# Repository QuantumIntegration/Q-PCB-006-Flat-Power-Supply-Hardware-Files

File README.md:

# Quantum DIY Kit Hardware Files - Flat Power Supply
## Introduction

This repository contains all the hardware files necessary to build the PCBs and assemble the DIY kits. The PCBs can be ordered from for example [JLCPCB](https://jlcpcb.com/) or [PCBWay](https://www.pcbway.com/). The components can be sourced mostly from [Amazon](https://amazon.com/) or [Digikey](https://digikey.com/), according to the links in the BOM file.

## Download the correct revision

If you are nor familiar with the git version control system, please follow these simple steps to download your version of the DIY kit

<em>1. Click the branch button</em>

<em>2. Select the branch matching your revision</em>

<em>3. Click the Code button</em>

<em>4. Download the ZIP and extract it on your machine</em>

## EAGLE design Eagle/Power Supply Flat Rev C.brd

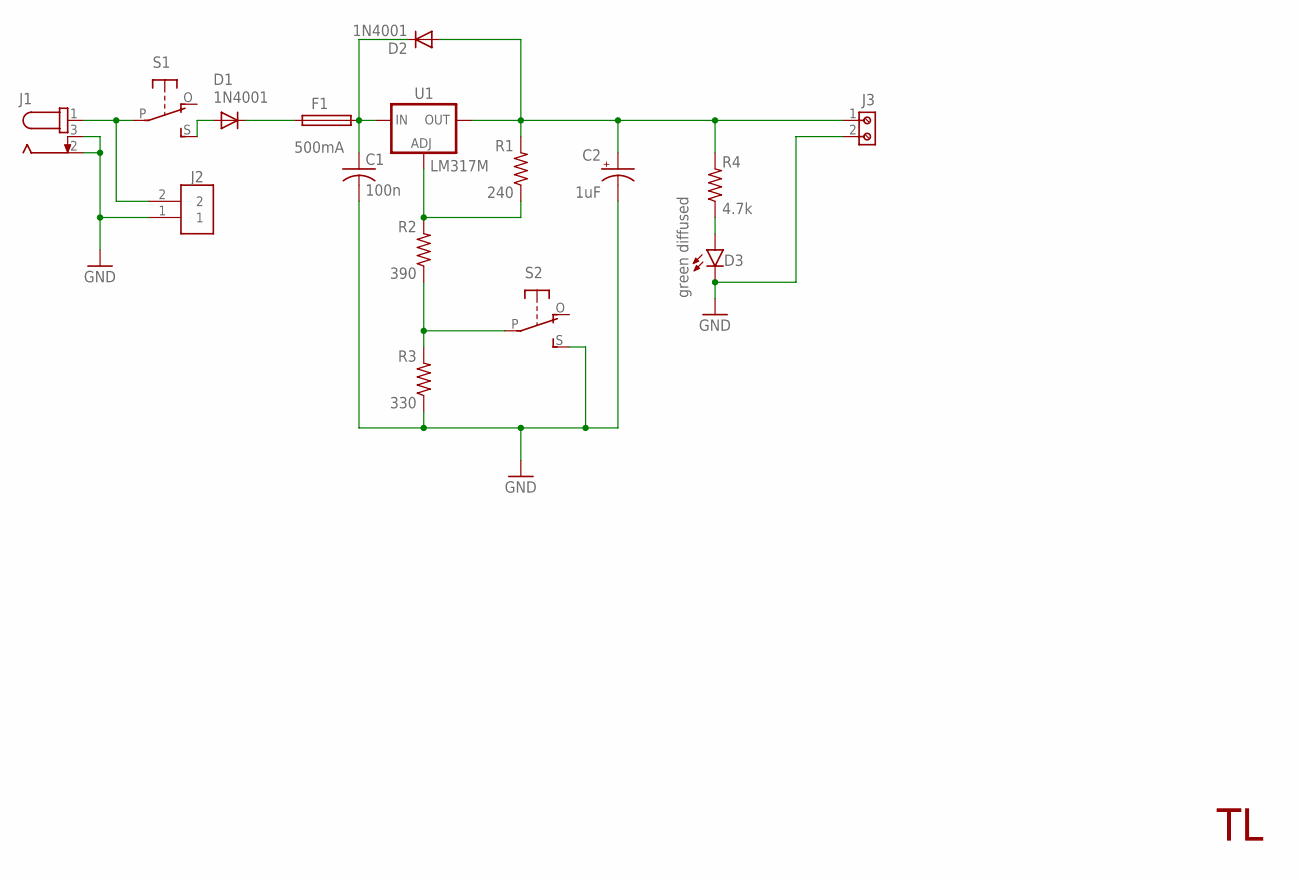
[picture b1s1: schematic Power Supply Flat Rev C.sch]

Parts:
C1: 100n; C050-024X044
C2: 1uF; E2-4
D1, D2: 1N4001; DO41-10
D3: green diffused; LED5MM
F1: 500mA; PTC-FUSE
J1: 694106301002
J2: 61300211121
J3: 691214110002
R1: 240; 0207/10
R2: 390; 0207/10
R3: 330; 0207/10
R4: 4.7k; 0207/10
S1, S2: SLIDE-SWITCHSIDE; EG1270-90
U1: LM317BENT; T03B; PARTNUMBER LM317M

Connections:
GND: C1.2, C2.-, D3.K (C), J1.2, J1.3, J2.1, J3.2, R3.1, S2.S
unnamed: D1.A, S1.S
unnamed: J1.1, J2.2, S1.P
unnamed: D1.C, F1.1
unnamed: C1.1, D2.C, F1.2, U1.3 (IN)
unnamed: R1.1, R2.2, U1.1 (ADJ)
unnamed: C2.+, D2.A, J3.1, R1.2, R4.2, U1.2 (OUT)
unnamed: R2.1, R3.2, S2.P
unnamed: D3.A, R4.1

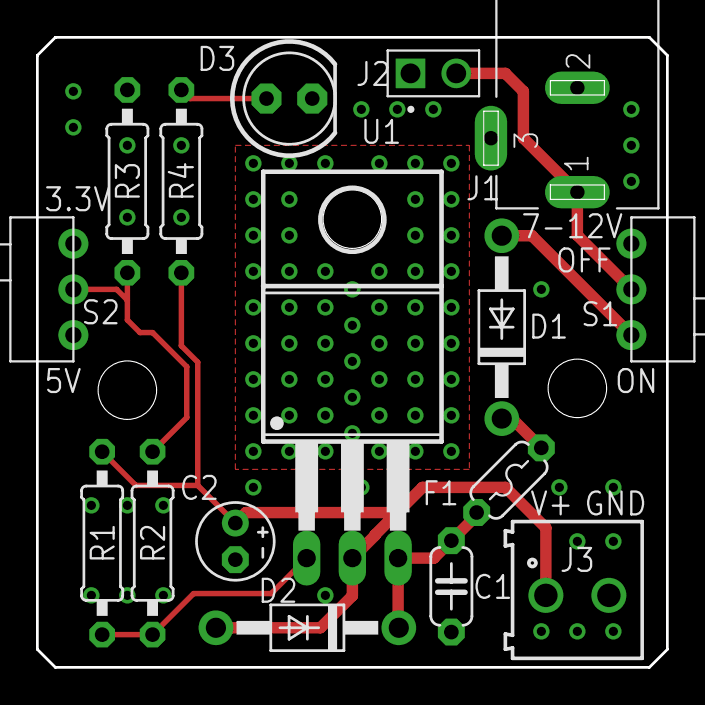
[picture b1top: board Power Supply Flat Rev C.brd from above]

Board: 2 copper layers, 35.0 x 35.0 mm, 16 parts (0 on the bottom side), 9 nets.

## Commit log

2021-07-12 iniital commit
2021-07-12 initial content
2021-12-17 added schematic

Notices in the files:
parts and their libraries:
Wurth_Connectors_WR-TBL Rising Cage Clam: Copyright: Würth Elektronik
